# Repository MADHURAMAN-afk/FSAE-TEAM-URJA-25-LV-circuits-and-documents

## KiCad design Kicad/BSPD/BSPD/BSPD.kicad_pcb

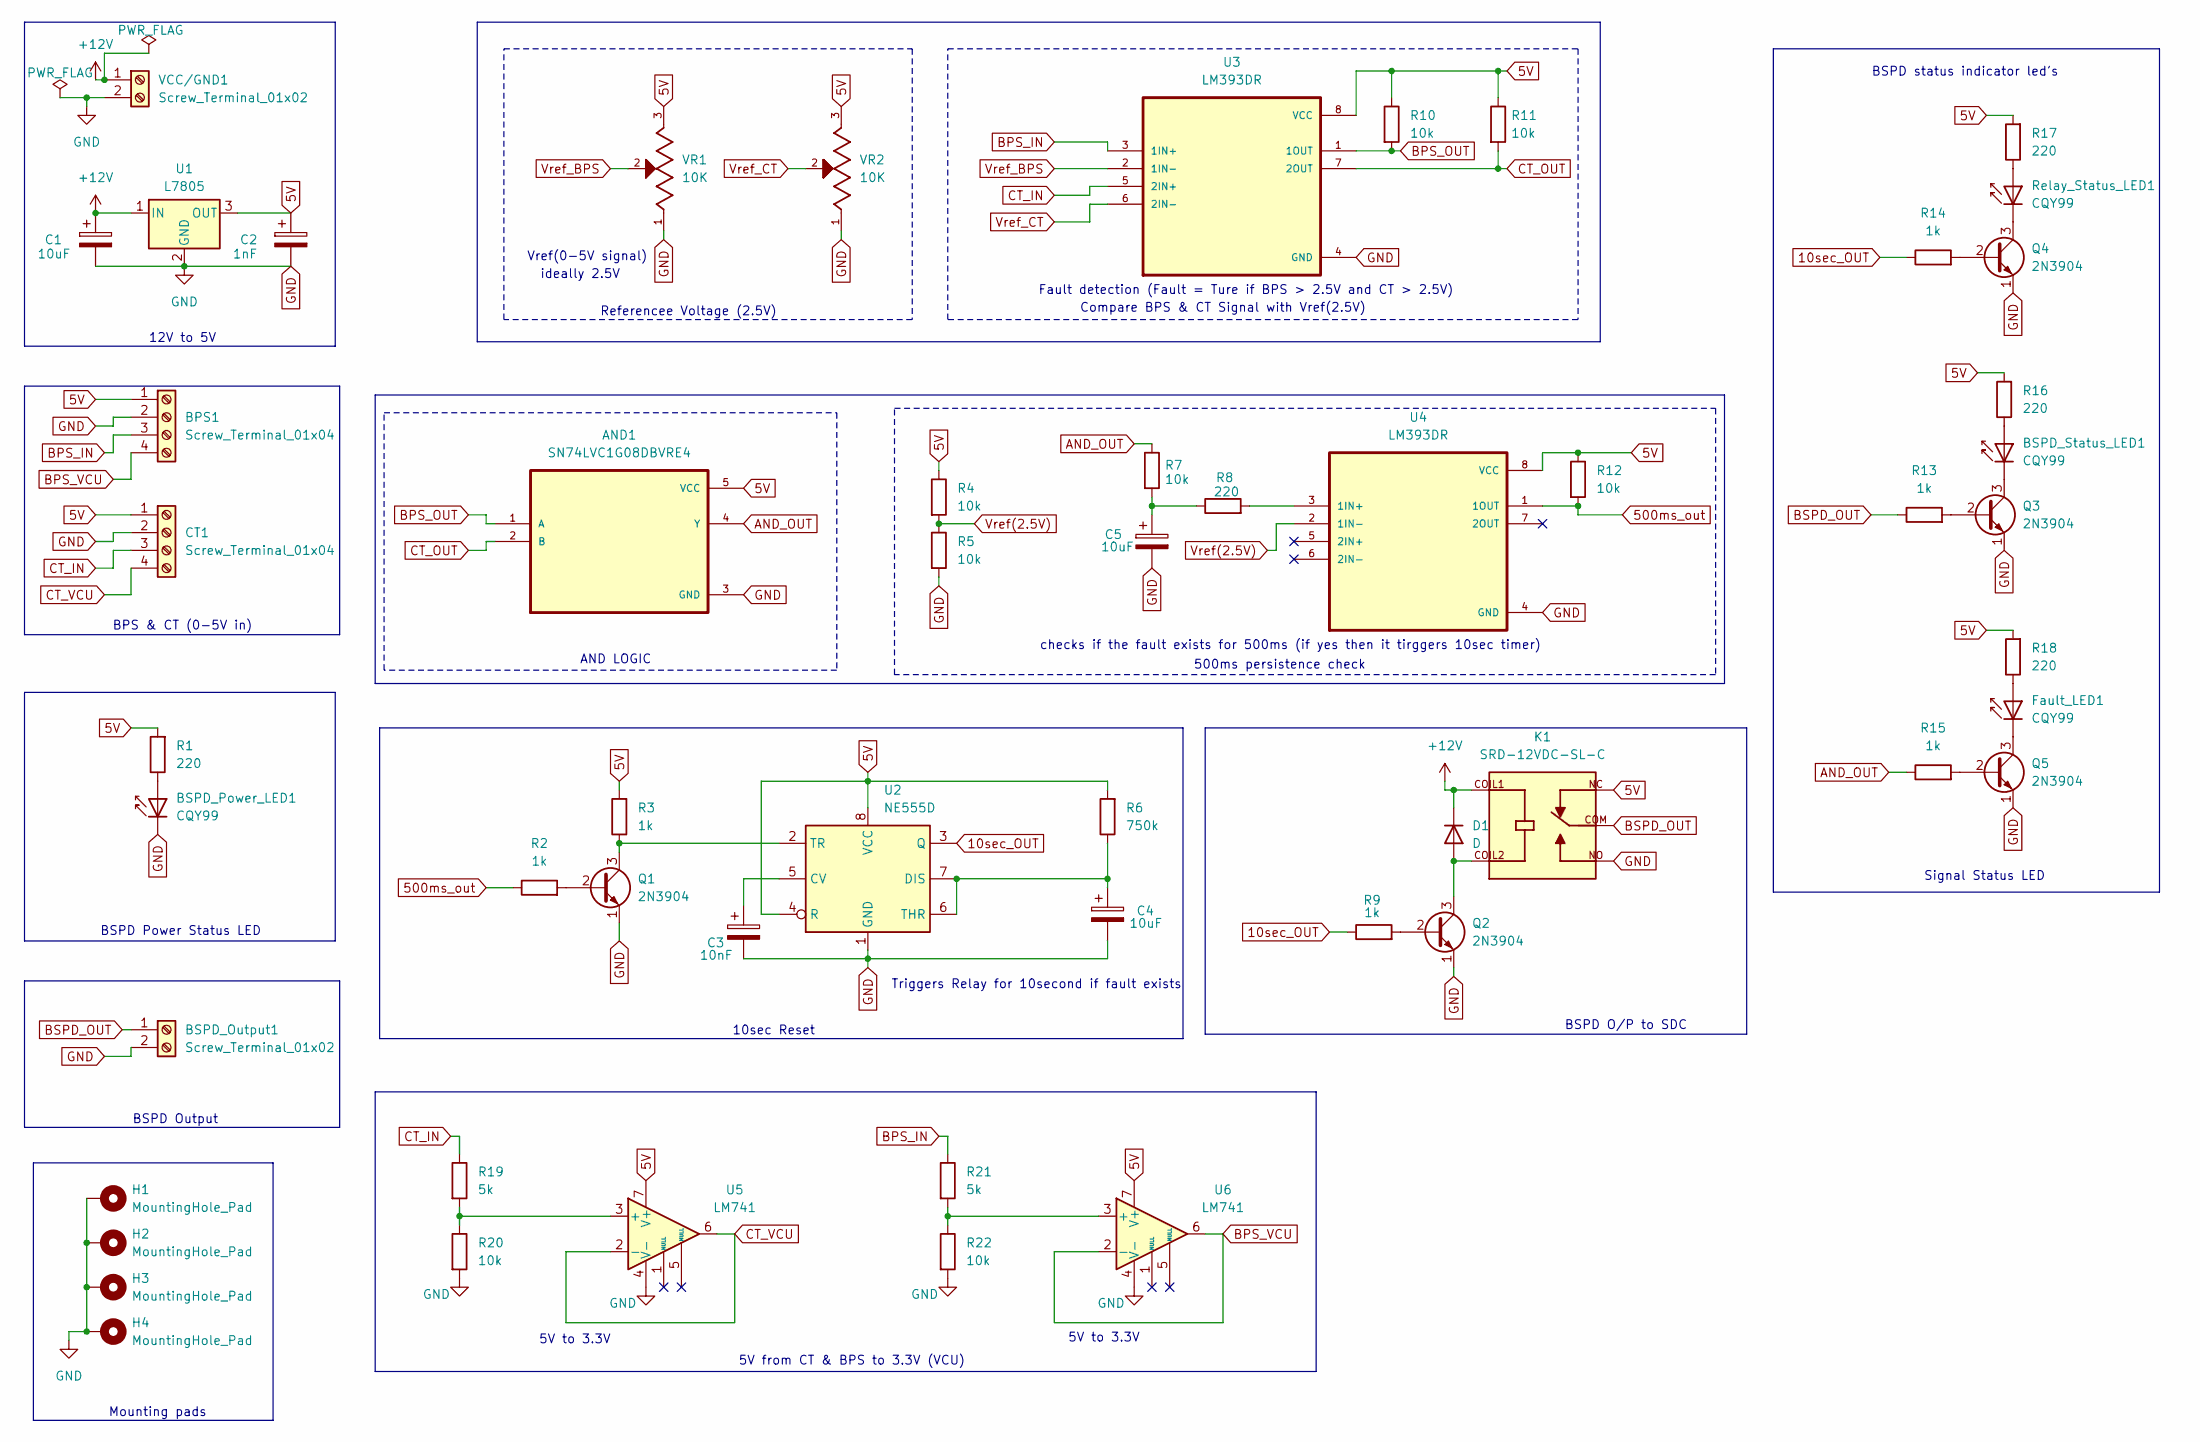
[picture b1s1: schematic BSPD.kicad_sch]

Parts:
AND1: SN74LVC1G08DBVRE4; SOT95P280X145-5N
BPS1: Screw_Terminal_01x04; PinHeader_1x04_P2.54mm_Vertical
BSPD_Output1: Screw_Terminal_01x02; PinHeader_1x02_P2.54mm_Vertical
BSPD_Power_LED1: CQY99; LED_D5.0mm_IRGrey
BSPD_Status_LED1: CQY99; LED_D5.0mm_IRGrey
C1, C4, C5: 10uF; CP_Radial_D4.0mm_P2.00mm
C2: 1nF; CP_Radial_D4.0mm_P2.00mm
C3: 10nF; CP_Radial_D4.0mm_P2.00mm
CT1: Screw_Terminal_01x04; PinHeader_1x04_P2.54mm_Vertical
D1: D; D_DO-35_SOD27_P7.62mm_Horizontal
Fault_LED1: CQY99; LED_D5.0mm_IRGrey
H1, H2, H3, H4: MountingHole_Pad; MountingHole_2.2mm_M2_ISO7380_Pad
K1: SRD-12VDC-SL-C; RELAY_SRD-12VDC-SL-C; PARTREV 1.0
Q1, Q2, Q3, Q4, Q5: 2N3904; TO-92_Inline
R1, R8, R16, R17, R18: 220; R_Axial_DIN0207_L6.3mm_D2.5mm_P10.16mm_Horizontal
R2, R3, R9, R13, R14, R15: 1k; R_Axial_DIN0207_L6.3mm_D2.5mm_P10.16mm_Horizontal
R4, R5, R7, R10, R11, R12: 10k; R_Axial_DIN0207_L6.3mm_D2.5mm_P10.16mm_Horizontal
R6: 750k; R_Axial_DIN0207_L6.3mm_D2.5mm_P10.16mm_Horizontal
R19, R21: 5k; R_Axial_DIN0204_L3.6mm_D1.6mm_P5.08mm_Horizontal
R20, R22: 10k; R_Axial_DIN0204_L3.6mm_D1.6mm_P5.08mm_Horizontal
Relay_Status_LED1: CQY99; LED_D5.0mm_IRGrey
U1: L7805; TO-220F-3_Horizontal_TabUp
U2: NE555D; DIP254P762X533-8
U3, U4: LM393DR; DIP794W45P254L959H508Q8
U5, U6: LM741; DIP794W45P254L959H508Q8
VCC/GND1: Screw_Terminal_01x02; PinHeader_1x02_P2.54mm_Vertical
VR1, VR2: 10K; TRIM_3296W-OT1-103LF; PARTREV 05/16

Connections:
5V: AND1.5 (VCC), BPS1.1, C2.1, CT1.1, K1.NC, R1.2, R3.2, R4.1, R6.2, R10.1, R11.1, R12.1, R16.2, R17.2, R18.2, U1.3 (OUT), U2.4 (R), U2.8 (VCC), U3.8 (VCC), U4.8 (VCC), U5.7 (V+), U6.7 (V+), VR1.3, VR2.3
10sec_OUT: R9.1, R14.1, U2.3 (Q)
500ms_out: R2.1, R12.2, U4.1 (1OUT)
+12V: C1.1, D1.1 (K), K1.COIL1, U1.1 (IN), VCC/GND1.1
AND_OUT: AND1.4 (Y), R7.1, R15.1
BPS_IN: BPS1.3, R21.1, U3.3 (1IN+)
BPS_OUT: AND1.1 (A), R10.2, U3.1 (1OUT)
BPS_VCU: BPS1.4, U6.2 (-), U6.6
BSPD_OUT: BSPD_Output1.1, K1.COM, R13.1
CT_IN: CT1.3, R19.1, U3.5 (2IN+)
CT_OUT: AND1.2 (B), R11.2, U3.7 (2OUT)
CT_VCU: CT1.4, U5.2 (-), U5.6
GND: AND1.3 (GND), BPS1.2, BSPD_Output1.2, BSPD_Power_LED1.1 (K), C1.2, C2.2, C3.2, C4.2, C5.2, CT1.2, H1.1, H2.1, H3.1, H4.1, K1.NO, Q1.1 (E), Q2.1 (E), Q3.1 (E), Q4.1 (E), Q5.1 (E), R5.2, R20.2, R22.2, U1.2 (GND), U2.1 (GND), U3.4 (GND), U4.4 (GND), U5.4 (V-), U6.4 (V-), VCC/GND1.2, VR1.1, VR2.1
unnamed: BSPD_Power_LED1.2 (A), R1.1
unnamed: BSPD_Status_LED1.2 (A), R16.1
unnamed: BSPD_Status_LED1.1 (K), Q3.3 (C)
unnamed: C5.1, R7.2, R8.1
unnamed: D1.2 (A), K1.COIL2, Q2.3 (C)
unnamed: Fault_LED1.2 (A), R18.1
unnamed: Fault_LED1.1 (K), Q5.3 (C)
unnamed: Q1.2 (B), R2.2
unnamed: Q1.3 (C), R3.1, U2.2 (TR)
unnamed: Q2.2 (B), R9.2
unnamed: Q3.2 (B), R13.2
unnamed: Q4.2 (B), R14.2
unnamed: Q4.3 (C), Relay_Status_LED1.1 (K)
unnamed: Q5.2 (B), R15.2
unnamed: R17.1, Relay_Status_LED1.2 (A)
unnamed: C3.1, U2.5 (CV)
unnamed: C4.1, R6.1, U2.6 (THR), U2.7 (DIS)
unnamed: R8.2, U4.3 (1IN+)
unnamed: R19.2, R20.1, U5.3 (+)
unnamed: R21.2, R22.1, U6.3 (+)
Vref(2.5V): R4.2, R5.1, U4.2 (1IN-)
Vref_BPS: U3.2 (1IN-), VR1.2
Vref_CT: U3.6 (2IN-), VR2.2

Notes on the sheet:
Triggers Relay for 10second if fault exists
BSPD Power Status LED
AND LOGIC
5V to 3.3V
BSPD O/P to SDC
checks if the fault exists for 500ms (if yes then it tirggers 10sec timer)
10sec Reset
BPS & CT (0-5V in)
Fault detection (Fault = Ture if BPS > 2.5V and CT > 2.5V)
12V to 5V
Signal Status LED
Compare BPS & CT Signal with Vref(2.5V)
5V from CT & BPS to 3.3V (VCU)
Vref(0-5V signal)
BSPD status indicator led's
ideally 2.5V
Referencee Voltage (2.5V)
BSPD Output
Mounting pads
500ms persistence check

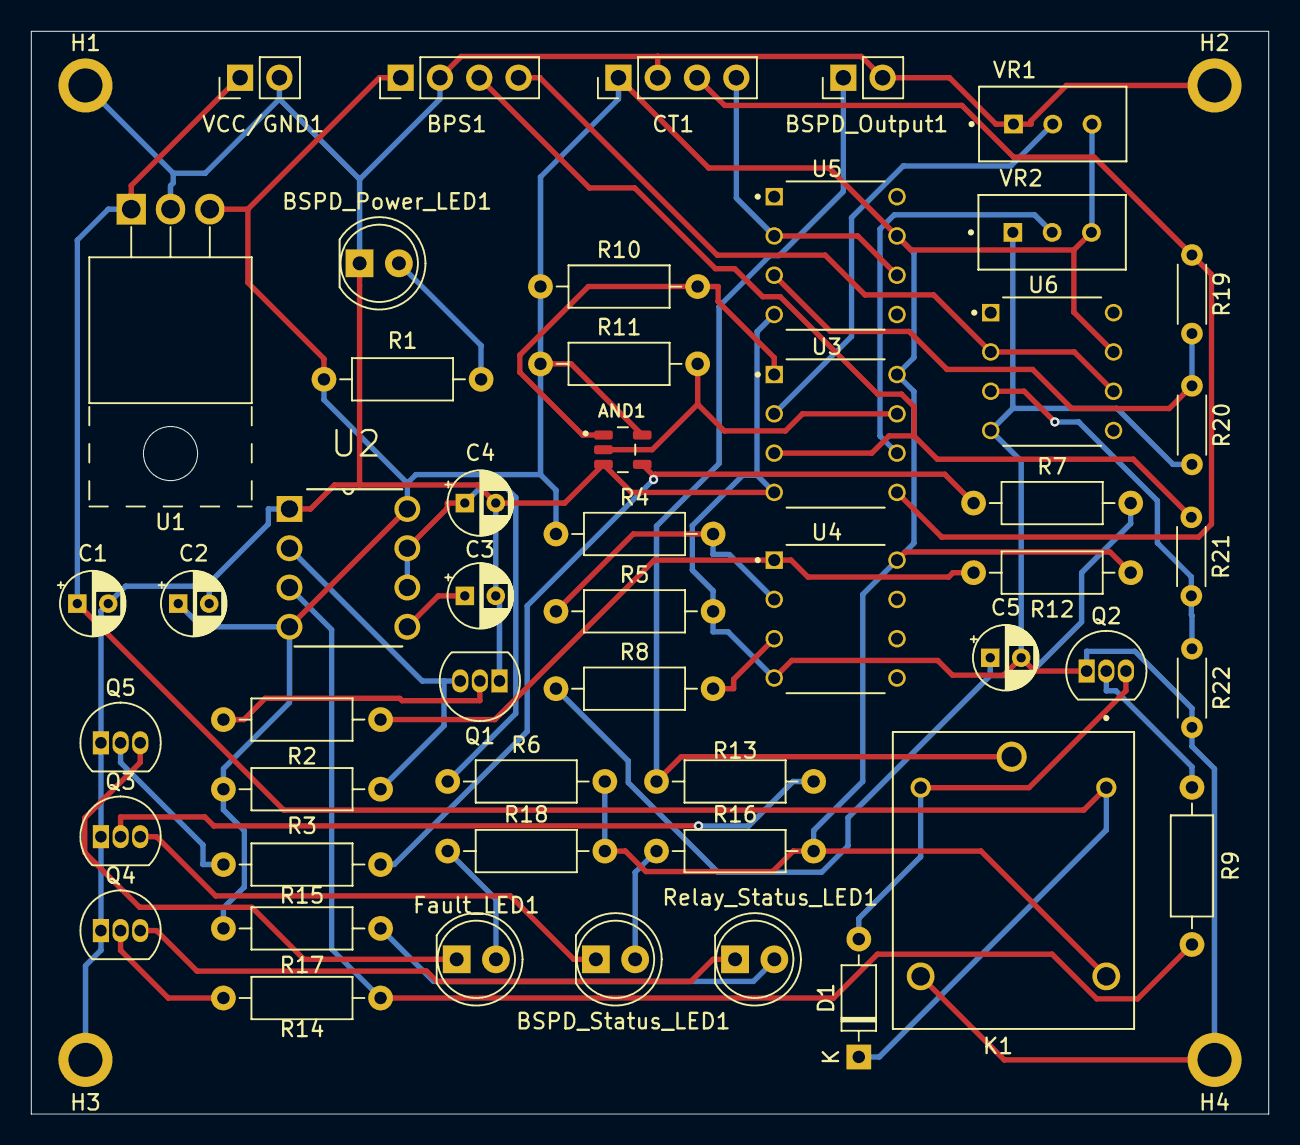
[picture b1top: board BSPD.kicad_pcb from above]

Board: 2 copper layers, 80.0 x 70.0 mm, 55 parts (0 on the bottom side), 36 nets.

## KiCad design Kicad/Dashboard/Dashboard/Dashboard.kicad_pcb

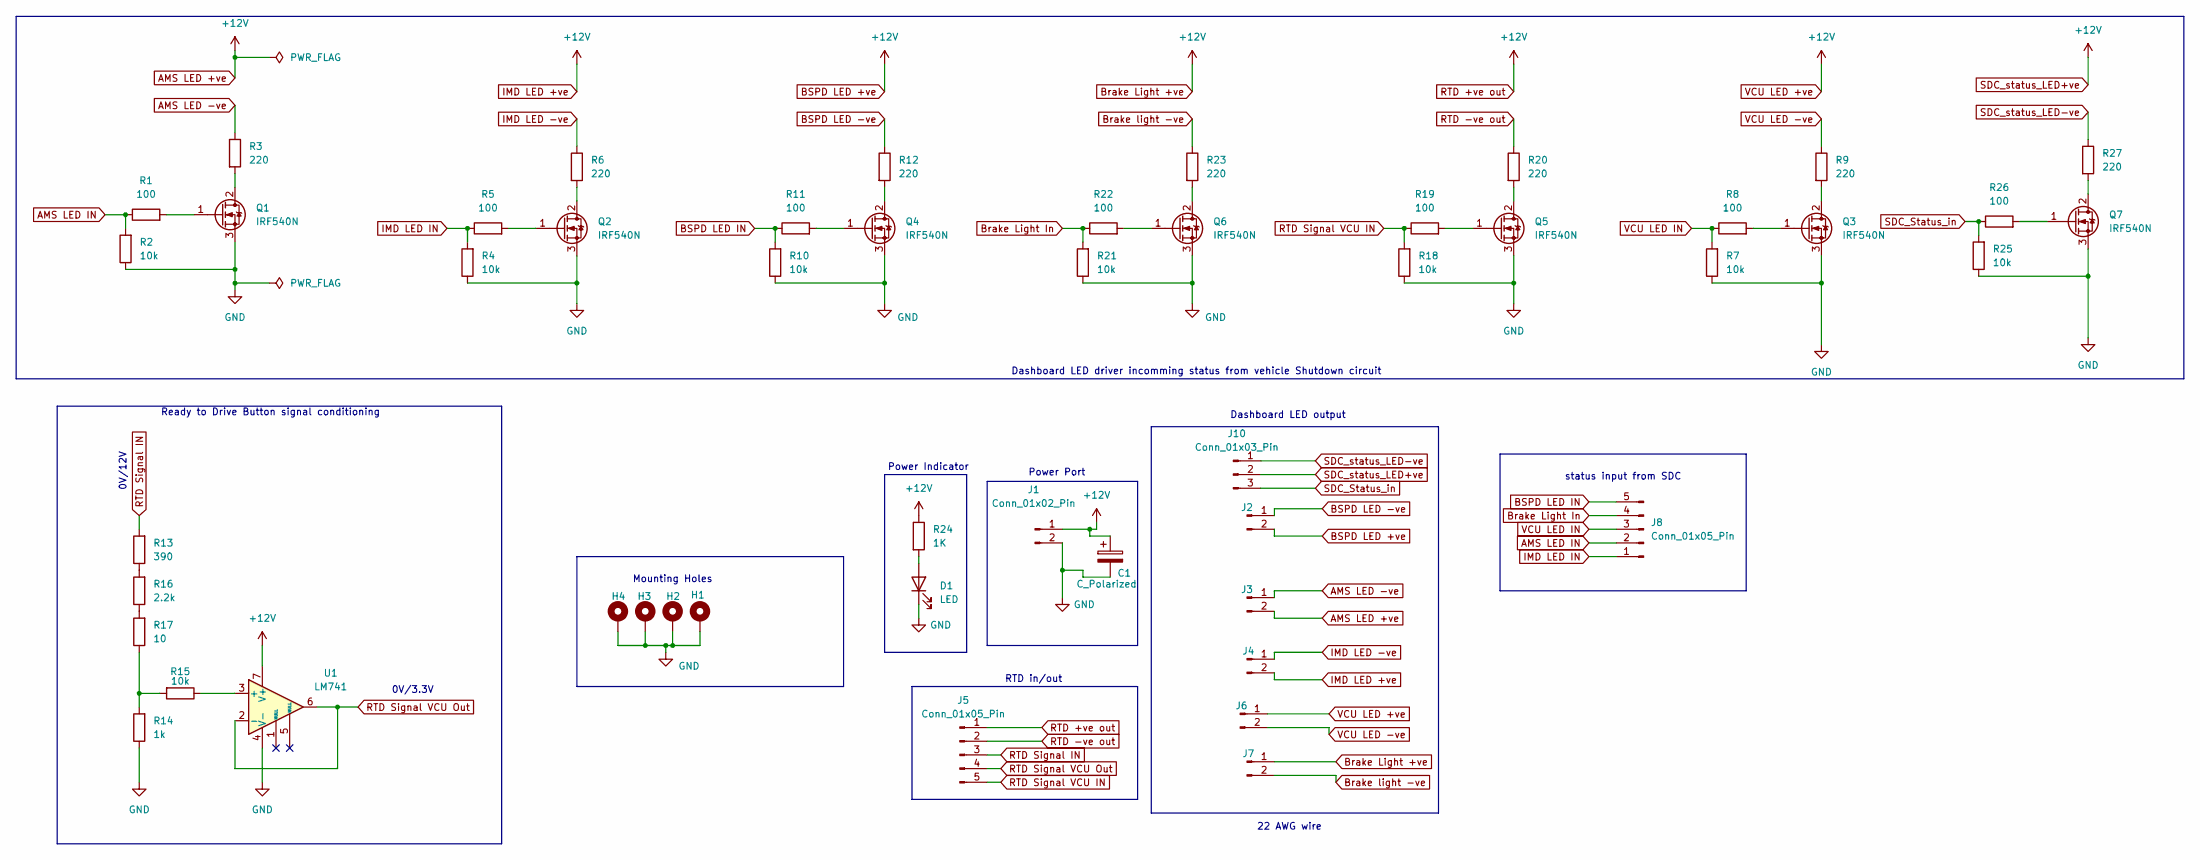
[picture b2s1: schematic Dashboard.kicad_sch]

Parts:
C1: C_Polarized; CP_Radial_D8.0mm_P5.00mm
D1: LED; LED_D5.0mm
H1, H2, H3, H4: MountingHole_Pad_MP; MountingHole_3.2mm_M3_ISO7380_Pad
J1, J2, J3, J4, J6, J7: Conn_01x02_Pin; PinHeader_1x02_P2.54mm_Vertical
J5, J8: Conn_01x05_Pin; PinHeader_1x05_P2.54mm_Vertical
J10: Conn_01x03_Pin; PinHeader_1x03_P2.54mm_Vertical
Q1, Q2, Q3, Q4, Q5, Q6, Q7: IRF540N; TO-220-3_Vertical
R1, R5, R8, R11, R19, R22, R26: 100; R_Axial_DIN0204_L3.6mm_D1.6mm_P7.62mm_Horizontal
R2, R4, R7, R10, R15, R18, R21, R25: 10k; R_Axial_DIN0204_L3.6mm_D1.6mm_P7.62mm_Horizontal
R3, R6, R9, R12, R20, R23, R27: 220; R_Axial_DIN0204_L3.6mm_D1.6mm_P7.62mm_Horizontal
R13: 390; R_Axial_DIN0204_L3.6mm_D1.6mm_P7.62mm_Horizontal
R14: 1k; R_Axial_DIN0204_L3.6mm_D1.6mm_P7.62mm_Horizontal
R16: 2.2k; R_Axial_DIN0204_L3.6mm_D1.6mm_P7.62mm_Horizontal
R17: 10; R_Axial_DIN0204_L3.6mm_D1.6mm_P7.62mm_Horizontal
R24: 1K; R_Axial_DIN0204_L3.6mm_D1.6mm_P7.62mm_Horizontal
U1: LM741; CERDIP-8_W7.62mm_SideBrazed_Socket

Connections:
AMS LED +ve: C1.1, J1.1, J2.2, J3.2, J4.2, J5.1, J6.1, J7.1, J10.2, R24.1, U1.7 (V+)
AMS LED -ve: J3.1, R3.1
AMS LED IN: J8.2, R1.1, R2.2
BSPD LED -ve: J2.1, R12.1
BSPD LED IN: J8.5, R10.2, R11.1
Brake Light In: J8.4, R21.2, R22.1
Brake light -ve: J7.2, R23.1
GND: C1.2, D1.1 (K), H1.MP, H2.MP, H3.MP, H4.MP, J1.2, Q1.3 (S), Q2.3 (S), Q3.3 (S), Q4.3 (S), Q5.3 (S), Q6.3 (S), Q7.3 (S), R2.1, R4.1, R7.1, R10.1, R14.1, R18.1, R21.1, R25.1, U1.4 (V-)
IMD LED -ve: J4.1, R6.1
IMD LED IN: J8.1, R4.2, R5.1
unnamed: D1.2 (A), R24.2
unnamed: Q1.2 (D), R3.2
unnamed: Q1.1 (G), R1.2
unnamed: Q2.2 (D), R6.2
unnamed: Q2.1 (G), R5.2
unnamed: Q3.2 (D), R9.2
unnamed: Q3.1 (G), R8.2
unnamed: Q4.2 (D), R12.2
unnamed: Q4.1 (G), R11.2
unnamed: Q5.2 (D), R20.2
unnamed: Q5.1 (G), R19.2
unnamed: Q6.2 (D), R23.2
unnamed: Q6.1 (G), R22.2
unnamed: Q7.2 (D), R27.2
unnamed: Q7.1 (G), R26.2
unnamed: R13.1, R16.2
unnamed: R14.2, R15.2, R17.1
unnamed: R16.1, R17.2
unnamed: R15.1, U1.3 (+)
RTD -ve out: J5.2, R20.1
RTD Signal IN: J5.3, R13.2
RTD Signal VCU IN: J5.5, R18.2, R19.1
RTD Signal VCU Out: J5.4, U1.2 (-), U1.6
SDC_Status_in: J10.3, R25.2, R26.1
SDC_status_LED-ve: J10.1, R27.1
VCU LED -ve: J6.2, R9.1
VCU LED IN: J8.3, R7.2, R8.1

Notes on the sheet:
Dashboard LED driver incomming status from vehicle Shutdown circuit
Mounting Holes
Ready to Drive Button signal conditioning
status input from SDC
0V/12V
Power Indicator
RTD in/out
Dashboard LED output
22 AWG wire
Power Port
0V/3.3V

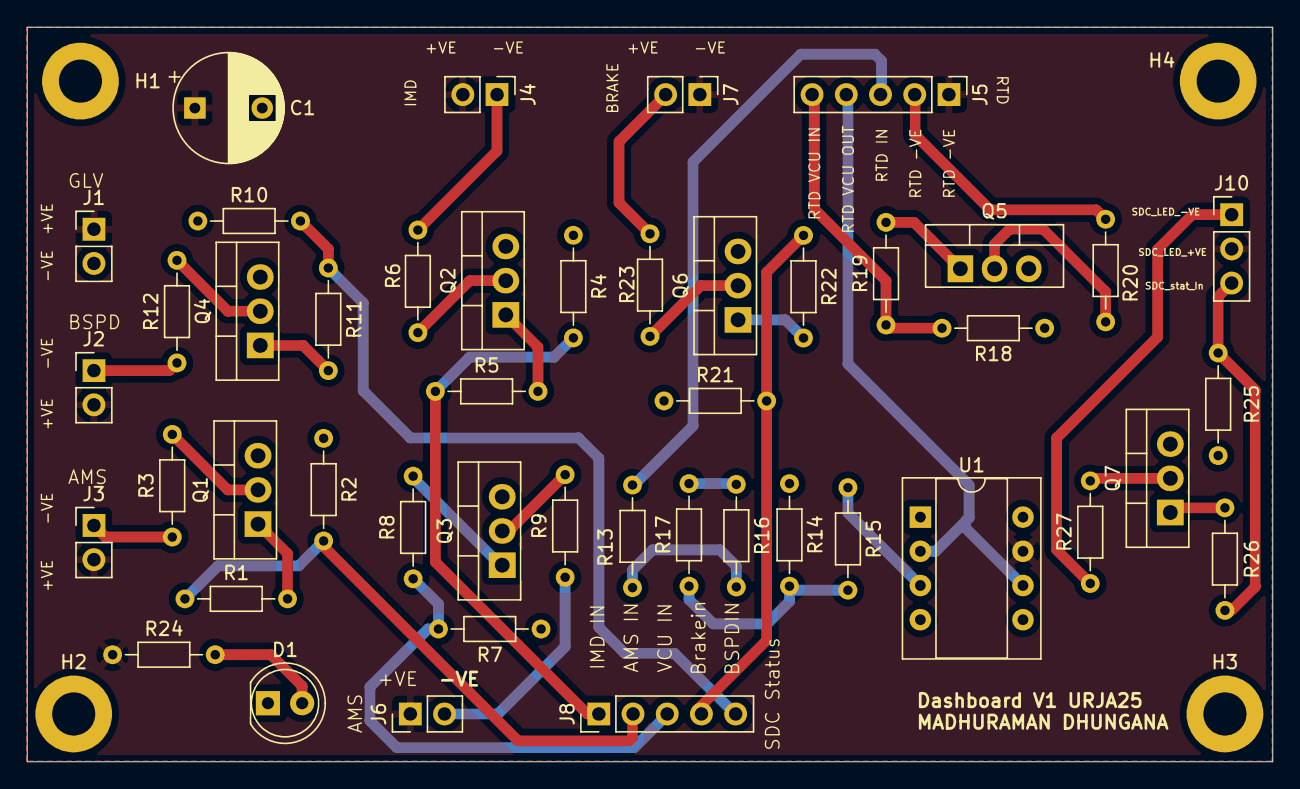
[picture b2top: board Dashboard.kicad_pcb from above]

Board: 2 copper layers, 92.5 x 54.6 mm, 50 parts (0 on the bottom side), 37 nets.

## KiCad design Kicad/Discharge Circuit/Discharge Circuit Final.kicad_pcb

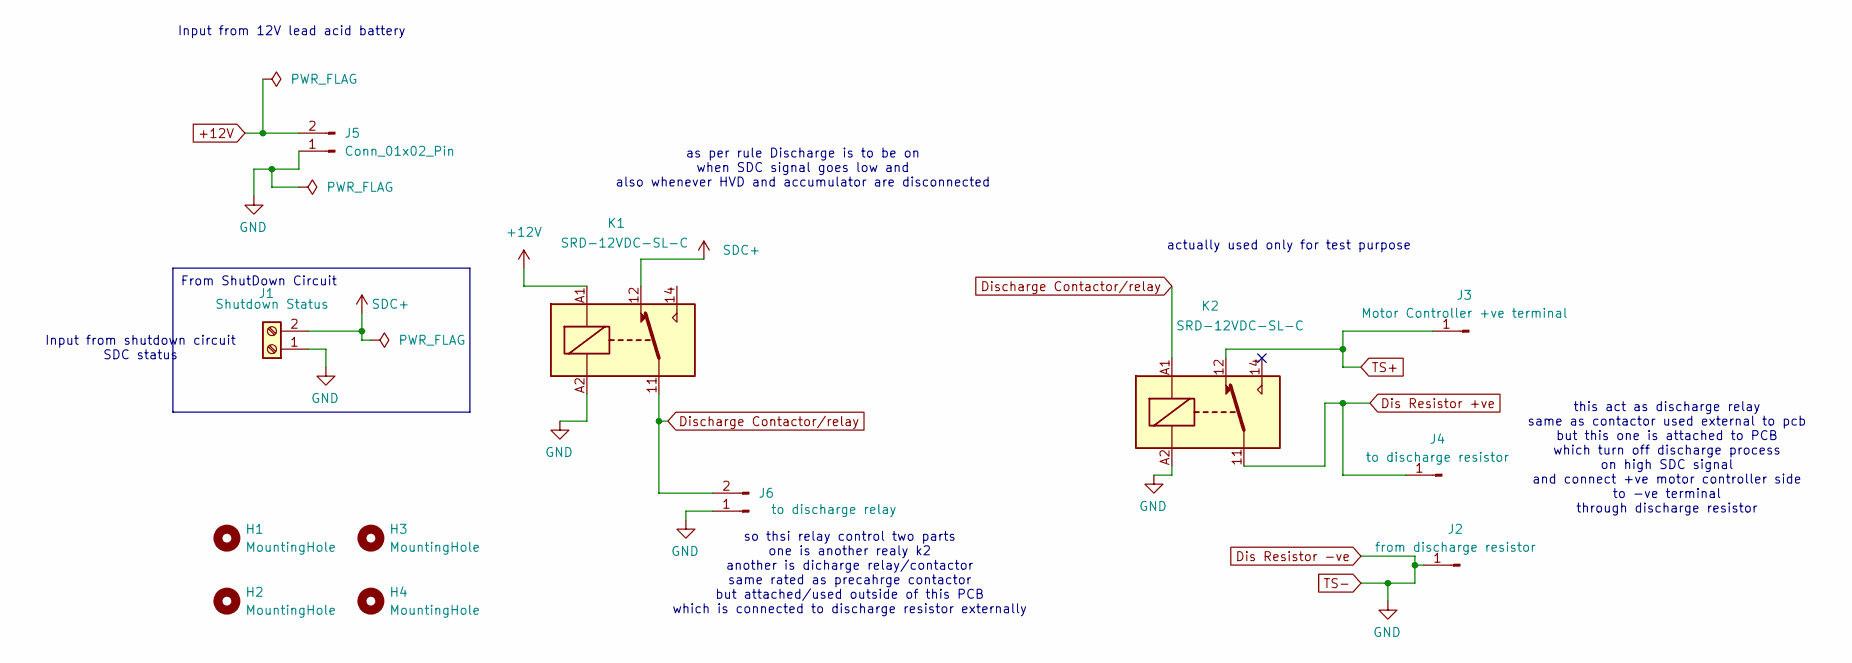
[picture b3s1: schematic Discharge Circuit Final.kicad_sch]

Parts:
H1, H2, H3, H4: MountingHole; MountingHole_4.3mm_M4
J1: Shutdown Status; TerminalBlock_Phoenix_MKDS-1,5-2-5.08_1x02_P5.08mm_Horizont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
J2: from discharge resistor; TerminalBlock_Phoenix_MKDS-1,5-2-5.08_1x02_P5.08mm_Horizont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
J3: Motor Controller +ve terminal; TerminalBlock_Phoenix_MKDS-1,5-2-5.08_1x02_P5.08mm_Horizont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
J4: to discharge resistor; TerminalBlock_Phoenix_MKDS-1,5-2-5.08_1x02_P5.08mm_Horizont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
J5: Conn_01x02_Pin; TerminalBlock_Phoenix_MKDS-1,5-2-5.08_1x02_P5.08mm_Horizont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
J6: to discharge relay; TerminalBlock_Phoenix_MKDS-1,5-2-5.08_1x02_P5.08mm_Horizont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
K1, K2: SRD-12VDC-SL-C; Relay_SPDT_Hongfa_HF3F-L-xx-1ZL1T

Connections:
+12V: J5.2, K1.A1
Dis Resistor +ve: J4.1, K2.11
Dis Resistor -ve: J1.1, J2.1, J5.1, J6.1, K1.A2, K2.A2
Discharge Contactor/relay: J6.2, K1.11, K2.A1
SDC+: J1.2, K1.12
TS+: J3.1, K2.12

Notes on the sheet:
From ShutDown Circuit
as per rule Discharge is to be on when SDC signal goes low and also whenever HVD and accumulator are disconnected
actually used only for test purpose
so thsi relay control two parts one is another realy k2 another is dicharge relay/contactor same rated as precahrge contactor but attached/used outside of this PCB which is connected to discharge resistor externally
Input from 12V lead acid battery
Input from shutdown circuit SDC status
this act as discharge relay same as contactor used external to pcb but this one is attached to PCB which turn off discharge process on high SDC signal and connect +ve motor controller side to -ve terminal through discharge resistor

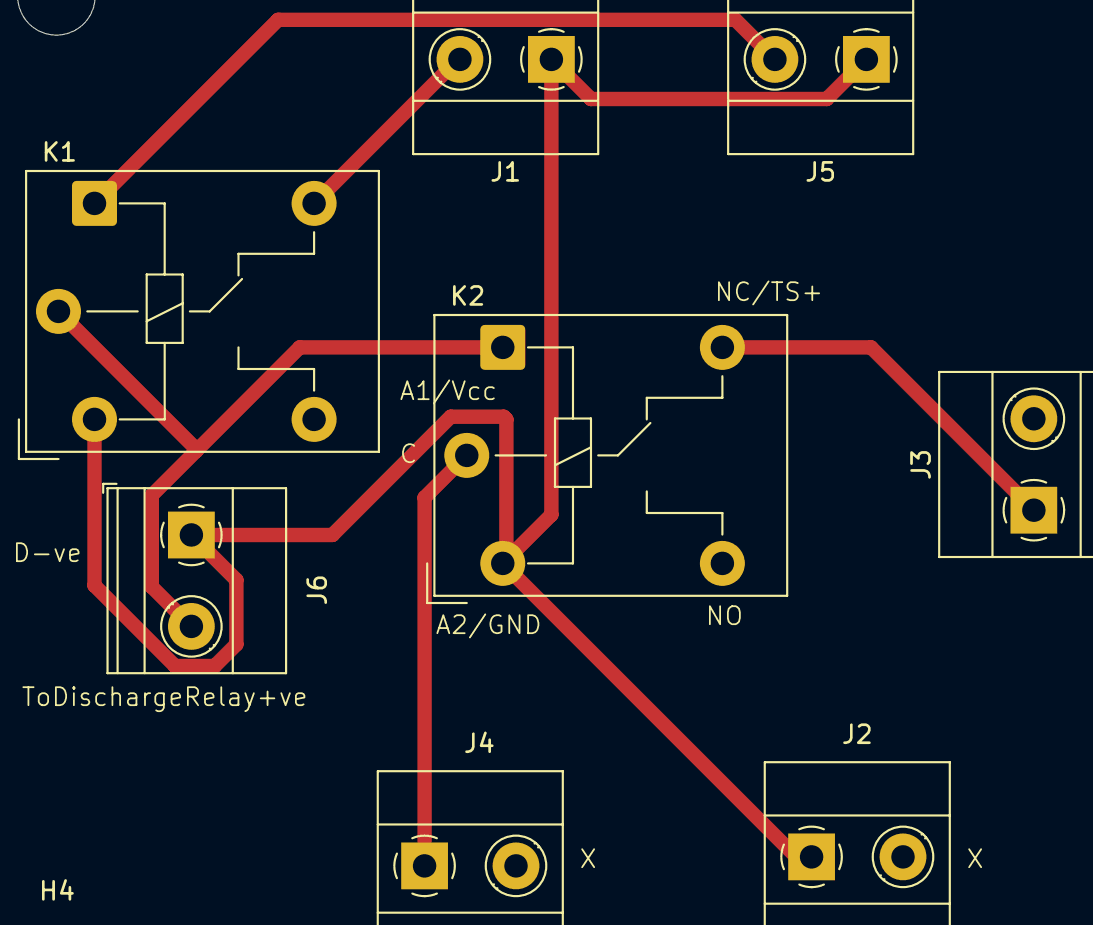
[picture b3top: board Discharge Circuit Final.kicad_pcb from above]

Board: 2 copper layers, 12 parts (0 on the bottom side), 6 nets.

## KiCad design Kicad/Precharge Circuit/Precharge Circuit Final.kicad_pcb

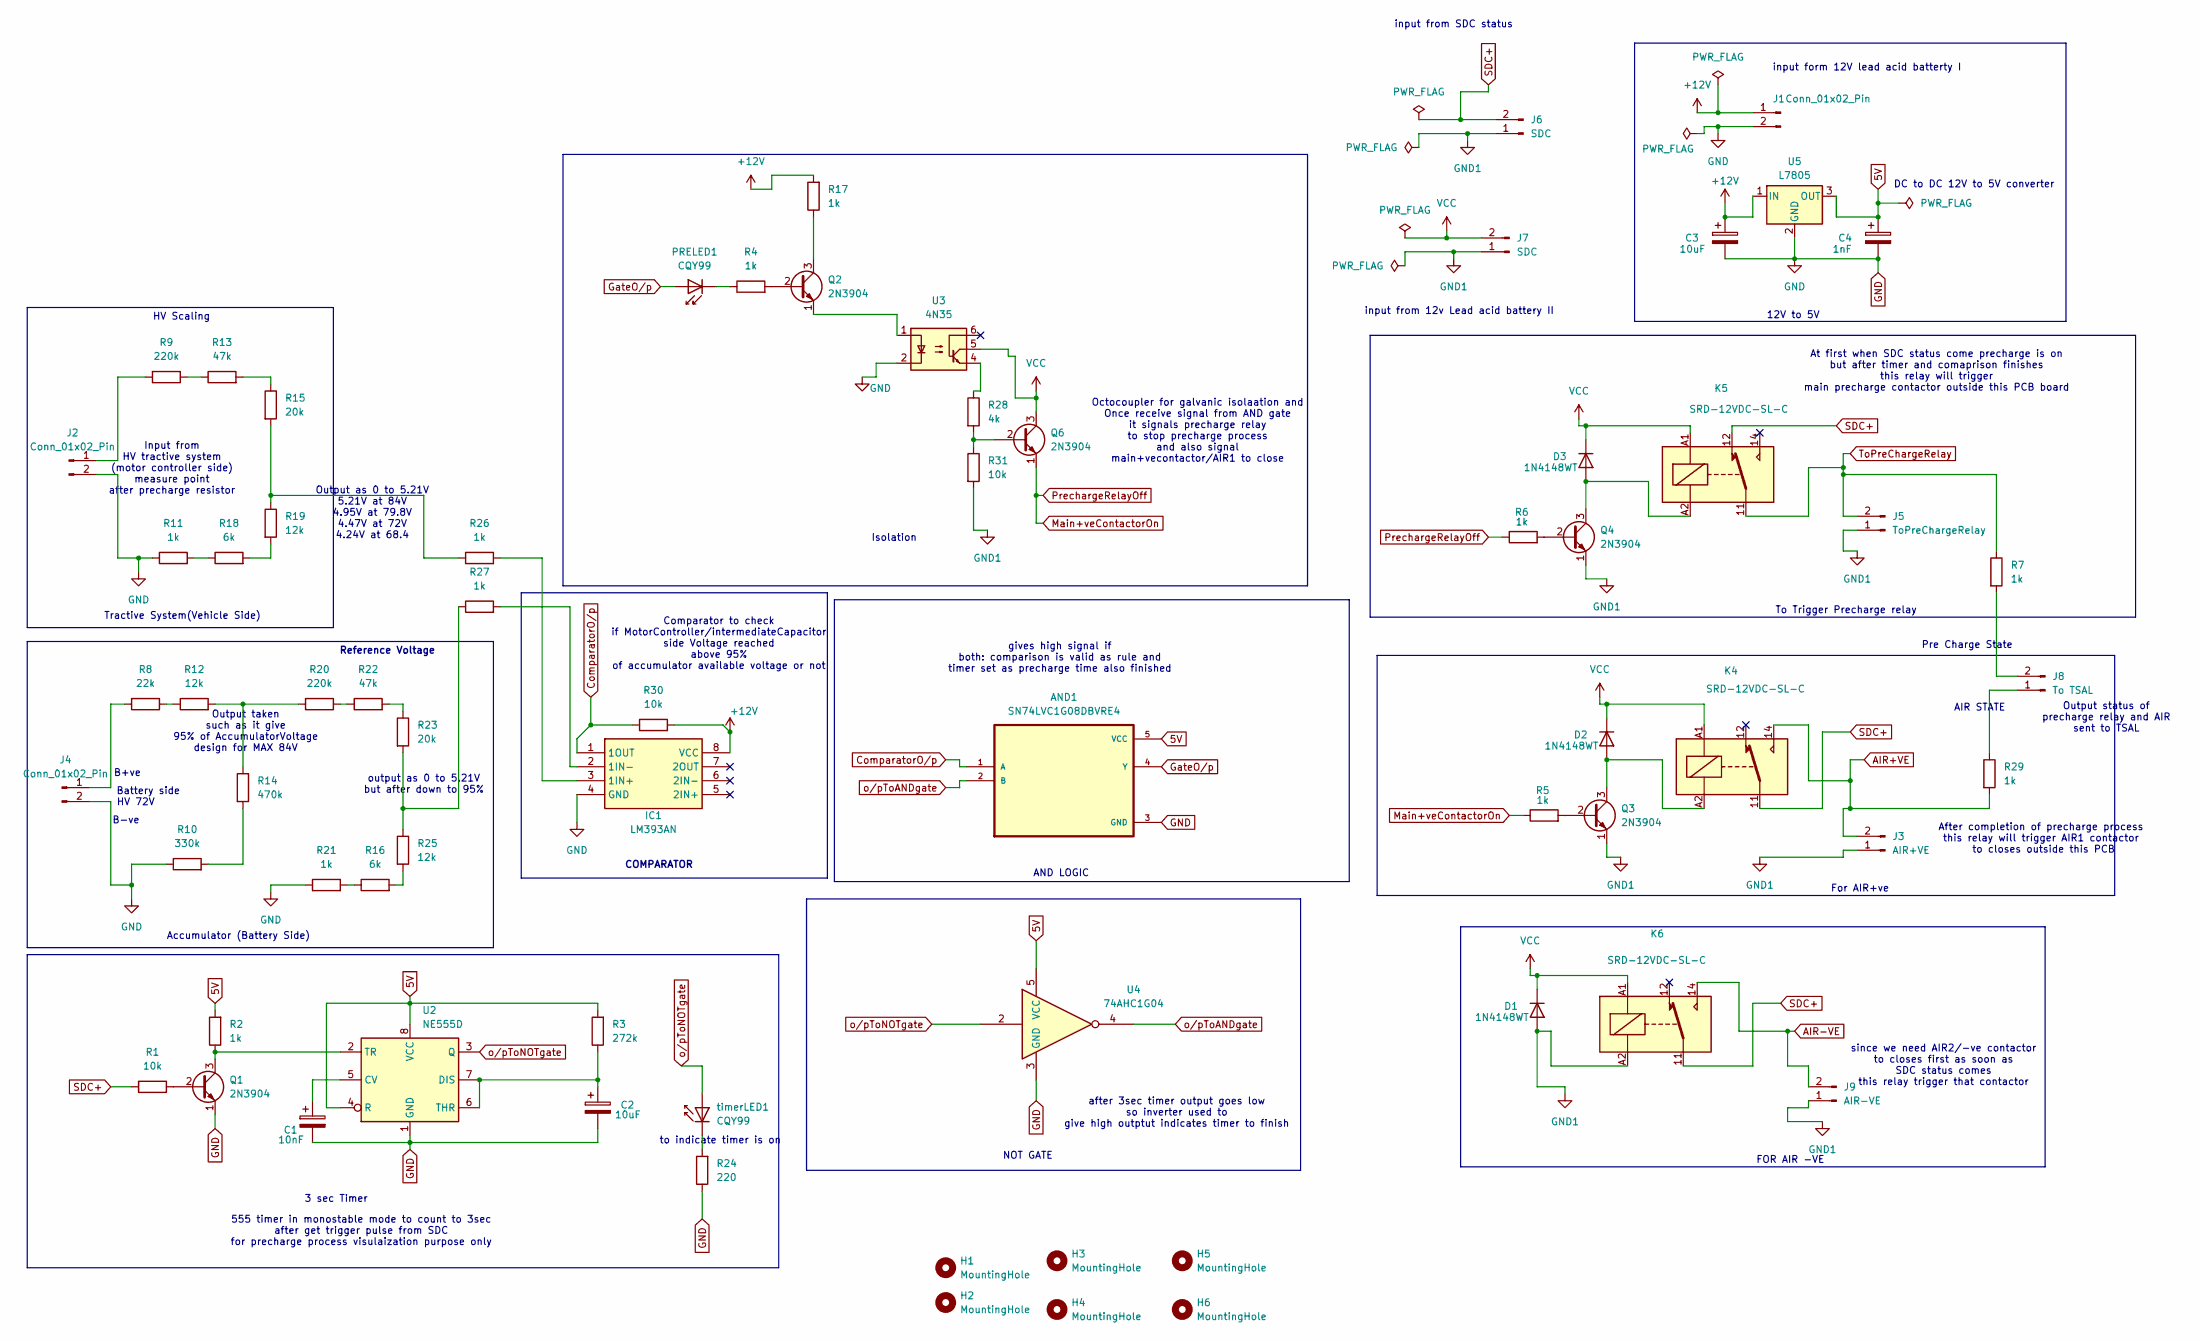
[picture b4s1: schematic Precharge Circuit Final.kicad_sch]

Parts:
AND1: SN74LVC1G08DBVRE4; SOT95P280X145-5N
C1: 10nF; CP_Radial_D4.0mm_P2.00mm
C2, C3: 10uF; CP_Radial_D4.0mm_P2.00mm
C4: 1nF; CP_Radial_D4.0mm_P2.00mm
D1, D2, D3: 1N4148WT; D_A-405_P7.62mm_Horizontal
H1, H2, H3, H4, H5, H6: MountingHole; MountingHole_4.3mm_M4
IC1: LM393AN; DIP-8_W7.62mm_Socket; Manufacturer_Part_Number LM393AN; Mouser Part Number N/A
J1, J2, J4: Conn_01x02_Pin; TerminalBlock_Phoenix_MKDS-1,5-2-5.08_1x02_P5.08mm_Horizont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
J3: AIR+VE; TerminalBlock_Phoenix_MKDS-1,5-2-5.08_1x02_P5.08mm_Horizont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
J5: ToPreChargeRelay; TerminalBlock_Phoenix_MKDS-1,5-2-5.08_1x02_P5.08mm_Horizont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
J6, J7: SDC; TerminalBlock_Phoenix_MKDS-1,5-2-5.08_1x02_P5.08mm_Horizont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
J8: To TSAL; TerminalBlock_Phoenix_MKDS-1,5-2-5.08_1x02_P5.08mm_Horizont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
J9: AIR-VE; TerminalBlock_Phoenix_MKDS-1,5-2-5.08_1x02_P5.08mm_Horizont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
K4, K5, K6: SRD-12VDC-SL-C; Relay_SPDT_Hongfa_HF3F-L-xx-1ZL1T
PRELED1: CQY99; LED_D5.0mm_IRGrey
Q1, Q2, Q3, Q4, Q6: 2N3904; TO-92_Inline_Wide
R1, R30, R31: 10k; R_Axial_DIN0207_L6.3mm_D2.5mm_P10.16mm_Horizontal
R2, R4, R5, R6, R7, R11, R17, R21, R26, R27, R29: 1k; R_Axial_DIN0207_L6.3mm_D2.5mm_P10.16mm_Horizontal
R3: 272k; R_Axial_DIN0207_L6.3mm_D2.5mm_P10.16mm_Horizontal
R8: 22k; R_Axial_DIN0207_L6.3mm_D2.5mm_P10.16mm_Horizontal
R9, R20: 220k; R_Axial_DIN0207_L6.3mm_D2.5mm_P10.16mm_Horizontal
R10: 330k; R_Axial_DIN0207_L6.3mm_D2.5mm_P10.16mm_Horizontal
R12, R19, R25: 12k; R_Axial_DIN0207_L6.3mm_D2.5mm_P10.16mm_Horizontal
R13, R22: 47k; R_Axial_DIN0207_L6.3mm_D2.5mm_P10.16mm_Horizontal
R14: 470k; R_Axial_DIN0207_L6.3mm_D2.5mm_P10.16mm_Horizontal
R15, R23: 20k; R_Axial_DIN0207_L6.3mm_D2.5mm_P10.16mm_Horizontal
R16, R18: 6k; R_Axial_DIN0207_L6.3mm_D2.5mm_P10.16mm_Horizontal
R24: 220; R_Axial_DIN0207_L6.3mm_D2.5mm_P10.16mm_Horizontal
R28: 4k; R_Axial_DIN0207_L6.3mm_D2.5mm_P10.16mm_Horizontal
U2: NE555D; DIP-8_W7.62mm
U3: 4N35; DIP-6_W7.62mm
U4: 74AHC1G04; SOT-23-5
U5: L7805; TO-220-3_Vertical
timerLED1: CQY99; LED_D5.0mm_IRGrey

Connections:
5V: AND1.5 (VCC), C4.1, R2.2, R3.2, U2.4 (R), U2.8 (VCC), U4.5 (VCC), U5.3 (OUT)
+12V: C3.1, IC1.8 (VCC), J1.1, R17.2, R30.2, U5.1 (IN)
AIR+VE: J3.2, K4.14, R29.2
AIR-VE: J9.2, K6.14
ComparatorO/p: AND1.1 (A), IC1.1 (1OUT), R30.1
GND: AND1.3 (GND), C1.2, C2.2, C3.2, C4.2, IC1.4 (GND), J1.2, J2.2, J4.2, Q1.1 (E), R10.1, R11.1, R21.1, R24.1, U2.1 (GND), U3.2, U4.3 (GND), U5.2 (GND)
GND1: D1.2 (A), J3.1, J5.1, J6.1, J7.1, J9.1, K6.A2, Q3.1 (E), Q4.1 (E), R31.2
GateO/p: AND1.4 (Y), PRELED1.2 (A)
Main+veContactorOn: Q6.1 (E), R5.1, R6.1
unnamed: D2.2 (A), K4.A2, Q3.3 (C)
unnamed: D3.2 (A), K5.A2, Q4.3 (C)
unnamed: IC1.3 (1IN+), R26.2
unnamed: IC1.2 (1IN-), R27.2
unnamed: J2.1, R9.2
unnamed: J4.1, R8.2
unnamed: J8.1, R29.1
unnamed: J8.2, R7.2
unnamed: PRELED1.1 (K), R4.1
unnamed: Q1.2 (B), R1.2
unnamed: Q1.3 (C), R2.1, U2.2 (TR)
unnamed: Q2.2 (B), R4.2
unnamed: Q2.3 (C), R17.1
unnamed: Q2.1 (E), U3.1
unnamed: Q3.2 (B), R5.2
unnamed: Q4.2 (B), R6.2
unnamed: Q6.2 (B), R28.2, R31.1
unnamed: R10.2, R14.2
unnamed: R11.2, R18.1
unnamed: R8.1, R12.1
unnamed: R12.2, R14.1, R20.2
unnamed: R9.1, R13.1
unnamed: R13.2, R15.1
unnamed: R15.2, R19.1, R26.1
unnamed: R16.1, R21.2
unnamed: R16.2, R25.2
unnamed: R18.2, R19.2
unnamed: R20.1, R22.1
unnamed: R22.2, R23.1
unnamed: R23.2, R25.1, R27.1
unnamed: R28.1, U3.4
unnamed: C1.1, U2.5 (CV)
unnamed: C2.1, R3.1, U2.6 (THR), U2.7 (DIS)
unnamed: R24.2, timerLED1.1 (K)
SDC+: J6.2, K4.11, K5.12, K6.11, R1.1
ToPreChargeRelay: J5.2, K5.11, R7.1
VCC: D1.1 (K), D2.1 (K), D3.1 (K), J7.2, K4.A1, K5.A1, K6.A1, Q6.3 (C), U3.5
o/pToANDgate: AND1.2 (B), U4.4
o/pToNOTgate: U2.3 (Q), U4.2, timerLED1.2 (A)

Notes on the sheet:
since we need AIR2/-ve contactor to closes first as soon as SDC status comes this relay trigger that contactor
B+ve
FOR AIR -VE
After completion of precharge process this relay will trigger AIR1 contactor to closes outside this PCB
Output taken such as it give 95% of AccumulatorVoltage design for MAX 84V
B-ve
Battery side
output as 0 to 5.21V but after down to 95%
COMPARATOR
Output status of precharge relay and AIR sent to TSAL
input from SDC status
NOT GATE
Comparator to check if MotorController/intermediateCapacitor side Voltage reached above 95% of accumulator available voltage or not
Isolation
At first when SDC status come precharge is on but after timer and comaprison finishes this relay will trigger main precharge contactor outside this PCB board
3 sec Timer
after 3sec timer output goes low so inverter used to give high outptut indicates timer to finish
Reference Voltage
Pre Charge State
12V to 5V
555 timer in monostable mode to count to 3sec after get trigger pulse from SDC for precharge process visulaization purpose only
gives high signal if both: comparison is valid as rule and timer set as precharge time also finished
input form 12V lead acid batterty I
Output as 0 to 5.21V 5.21V at 84V 4.95V at 79.8V 4.47V at 72V 4.24V at 68.4
AIR STATE
DC to DC 12V to 5V converter
Tractive System(Vehicle Side)
HV 72V
Octocoupler for galvanic isolaation and Once receive signal from AND gate it signals precharge relay to stop precharge process and also signal main+vecontactor/AIR1 to close
HV Scaling
Input from HV tractive system (motor controller side) measure point after precharge resistor
For AIR+ve
AND LOGIC
to indicate timer is on
Accumulator (Battery Side)
To Trigger Precharge relay
input from 12v Lead acid battery II

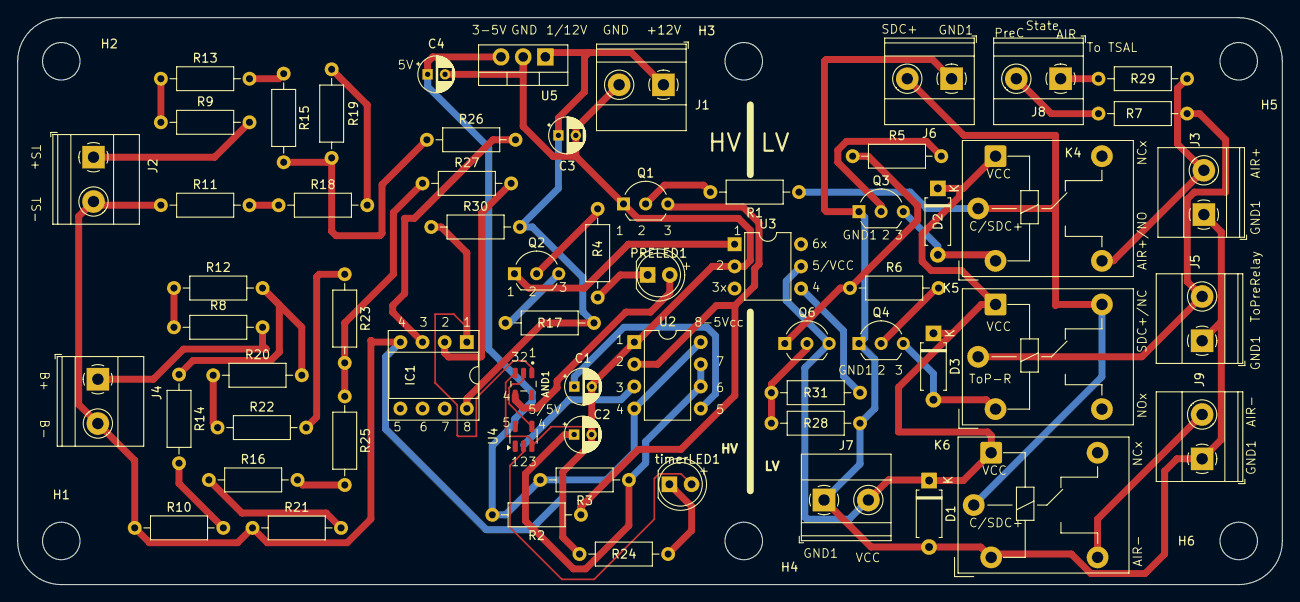
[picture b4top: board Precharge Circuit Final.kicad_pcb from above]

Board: 2 copper layers, 145.0 x 65.0 mm, 69 parts (0 on the bottom side), 48 nets.
